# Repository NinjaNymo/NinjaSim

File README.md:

# NinjaSim
A repository for flight simulation stuff, ranging from hardware designs, firmware for said designs, keybind configurations and helpfull scripts.

- `hw/` store KiCad hardware designs and mechanical models.
- `fw/` store firmware for hardware designs.
- `cfg/` store simulator keybinds, HOTAS configurations and OpenTrack profiles. 
- `tools/` store scripts etc.

## Relevant Repostories
- [`NinjaEcadLib`](https://github.com/ninjanymo/ninjaecadlib) - Component library for all hardware designs.
- [`NinjaSim-CDT`](https://github.com/ninjanymo/ninjasim-cdt) - Documentation on how to integrate custom projects into Virpil Control's CDT range of products.

# Overview

## NinjaSim LED Power Board
An adjustable constant current LED driver board desiged for driving three external series IR LEDs for OpenTrack head tracking.

Adjustable current regulation is achieved through an anlog _Voltage-to-Current_ (V-I) regulator. Battery charging is achieved through TI's BQ25185 integrated charger IC where low charging currents are set for safe operation.

Both versions are 2-layered designs with conservative constraints and make extensive use of JLCPCB _Basic Parts_ for cost effective manufacturing.

The two versions differ only in form factor and connector choices.

### `hw/nsim-lpb-v1`

### `hw/nsim-lpb-v2`

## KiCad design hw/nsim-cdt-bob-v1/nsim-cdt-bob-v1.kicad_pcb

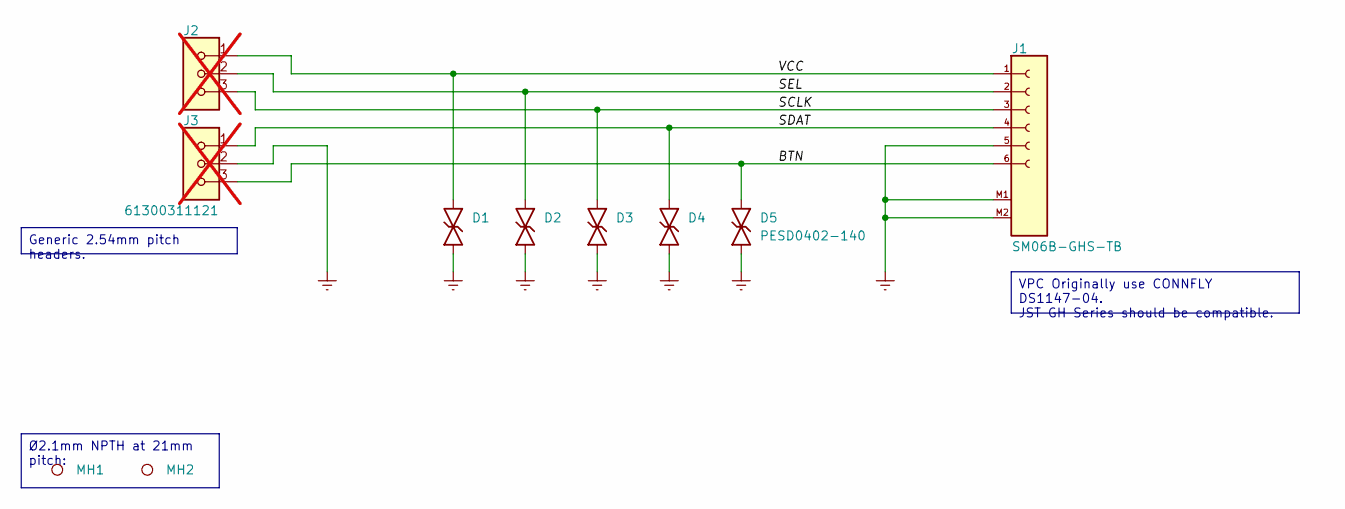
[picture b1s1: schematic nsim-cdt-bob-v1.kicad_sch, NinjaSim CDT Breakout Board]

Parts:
D1, D2, D3, D4, D5: PESD0402-140; RESC1005X45N; Manufacturer_PN PESD0402-140
J1: SM06B-GHS-TB; JST_SM06B-GHS-TB; Manufacturer_PN SM06B-GHS-TB
J2, J3: 61300311121; HDR_254P_03POS_TH_Wurth_WR-PHD; Manufacturer_PN 61300311121; not fitted
MH1, MH2: MH_NPTH_CIR2100

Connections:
/BTN: D5.2 (A), J1.6, J3.3
/SCLK: D3.2 (A), J1.3, J2.3
/SDAT: D4.2 (A), J1.4, J3.1
/SEL: D2.2 (A), J1.2, J2.2
/VCC: D1.2 (A), J1.1, J2.1
GND: D1.1 (K), D2.1 (K), D3.1 (K), D4.1 (K), D5.1 (K), J1.5, J1.M1, J1.M2, J3.2

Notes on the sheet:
Ø2.1mm NPTH at 21mm pitch:
VPC Originally use CONNFLY DS1147-04. JST GH Series should be compatible.
Generic 2.54mm pitch headers.

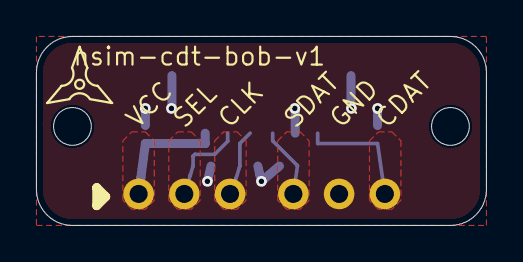
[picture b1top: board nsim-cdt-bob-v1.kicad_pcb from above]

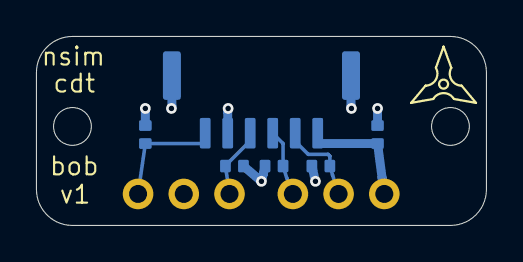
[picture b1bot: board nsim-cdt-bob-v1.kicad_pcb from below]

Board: 2 copper layers, 25.0 x 10.5 mm, 10 parts (6 on the bottom side), 6 nets.

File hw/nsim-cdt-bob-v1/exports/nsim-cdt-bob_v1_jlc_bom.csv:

"Designator","Comment","LCSC Part Number","Package"
"J1","SM06B-GHS-TB","",""
"D5","PESD0402-140","",""
"D4","PESD0402-140","",""
"D3","PESD0402-140","",""
"D2","PESD0402-140","",""
"D1","PESD0402-140","",""
"J3","61300311121","",""
"J2","61300311121","",""

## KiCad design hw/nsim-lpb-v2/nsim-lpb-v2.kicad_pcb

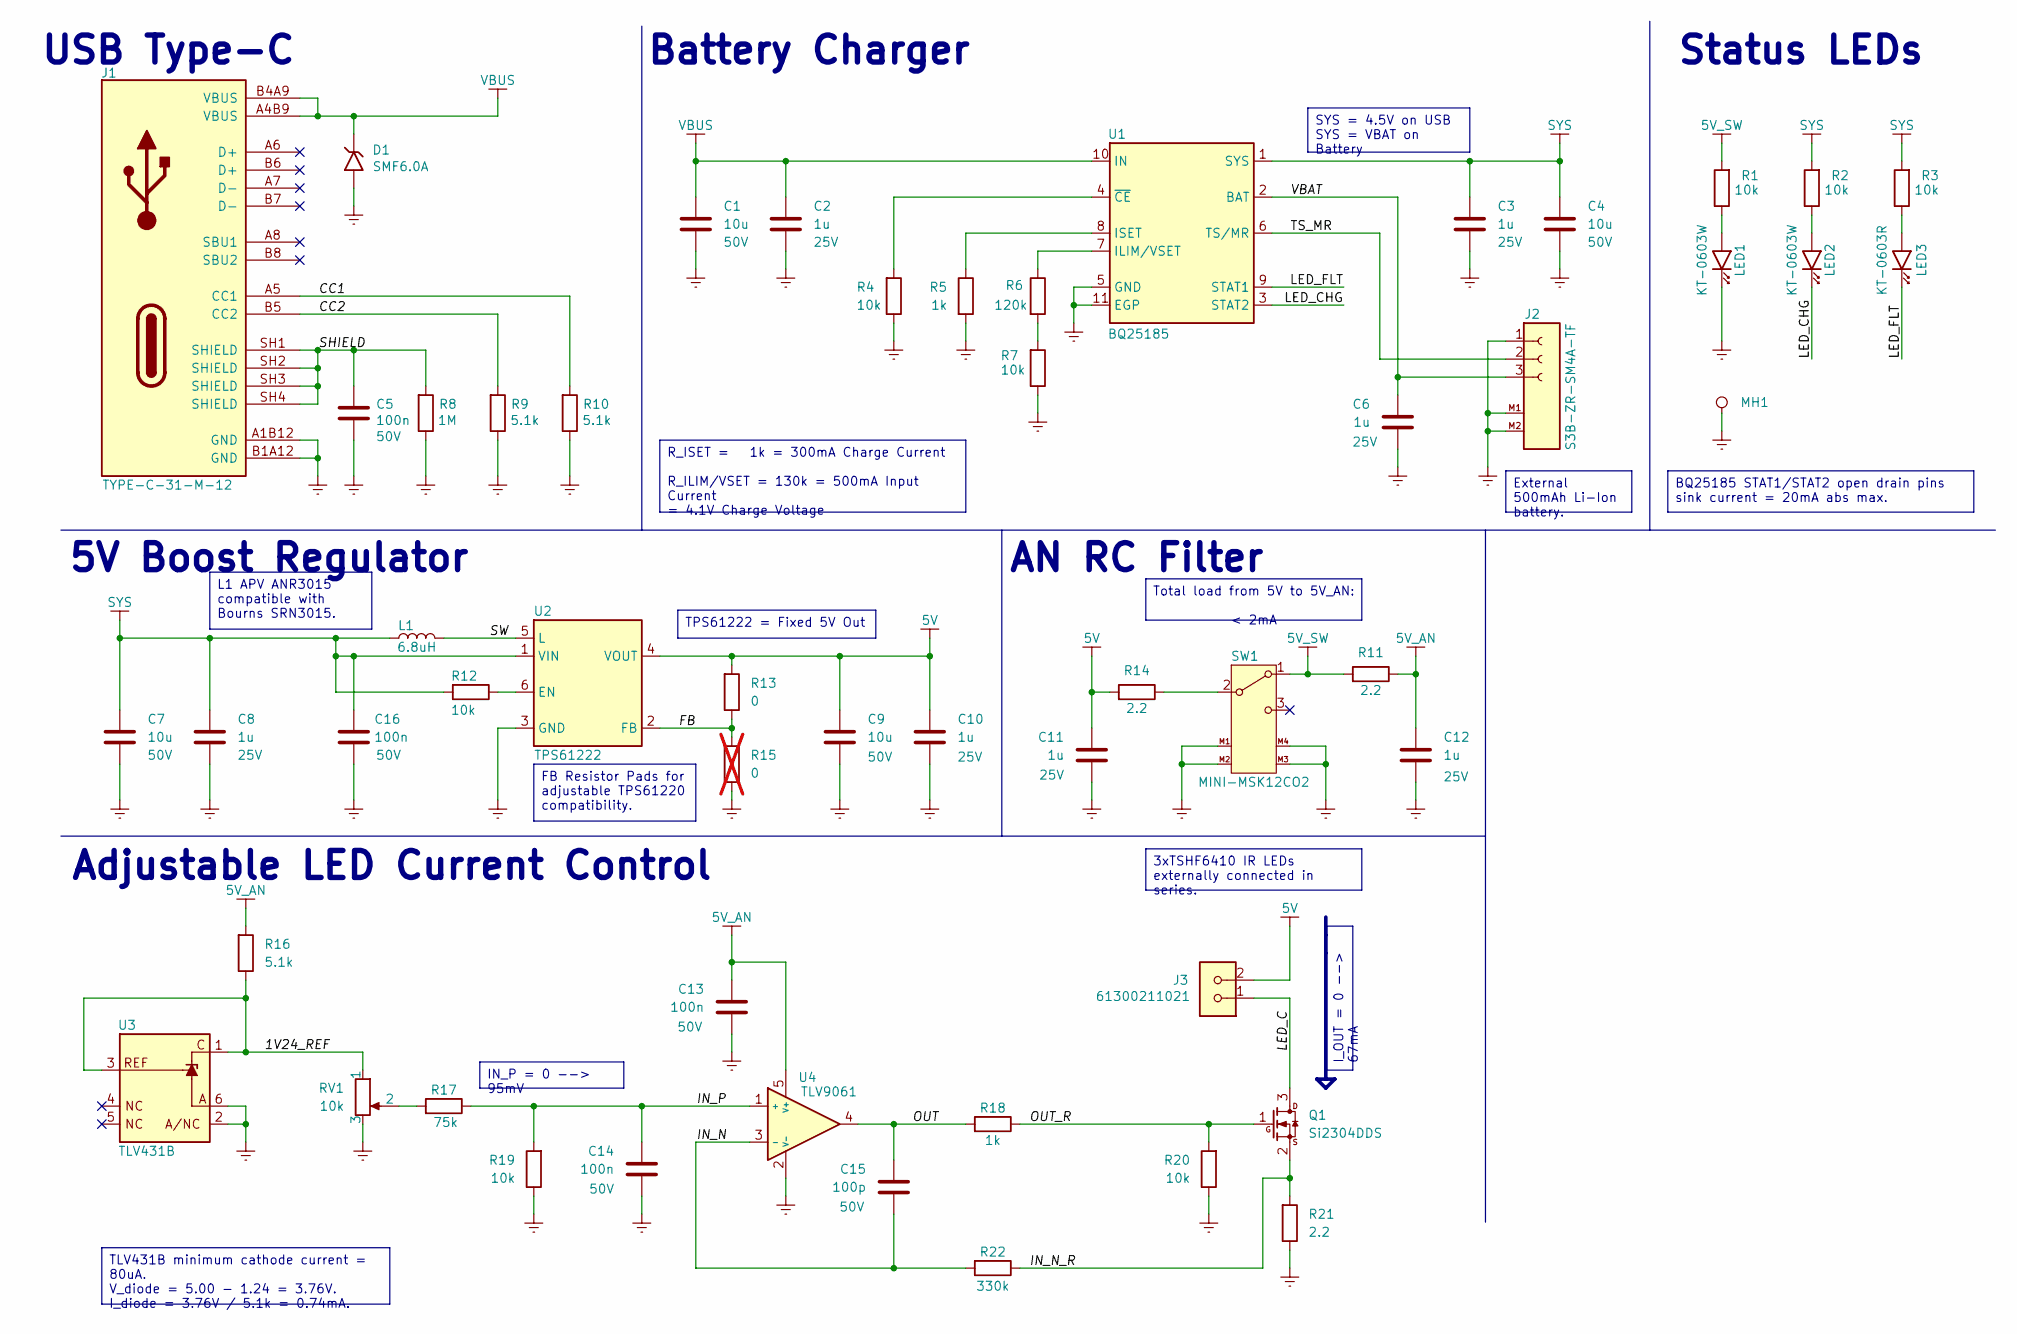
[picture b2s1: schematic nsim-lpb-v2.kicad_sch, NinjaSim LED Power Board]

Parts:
C1, C4, C7, C9: 10u; CAPC3216X180N; Manufacturer_PN CL31A106KBHNNNE; JLC_Package C1206
C2, C3, C6, C8, C10, C11, C12: 1u; CAPC1005X60N; Manufacturer_PN CL05A105KA5NQNC; JLC_Package C0402
C5, C13, C14, C16: 100n; CAPC1005X55N; Manufacturer_PN CL05B104KB54PNC; JLC_Package C0402
C15: 100p; CAPC1005X55N; Manufacturer_PN 0402CG101J500NT; JLC_Package C0402
D1: SMF6.0A; SODFL365X175X110N; Manufacturer_PN SMF6.0A; JLC_Package SOD-123FL
J1: TYPE-C-31-M-12; HRO_TYPE-C-31-M-12; Manufacturer_PN TYPE-C-31-M-12; JLC_Package SMD
J2: S3B-ZR-SM4A-TF; JST_S3B-ZR-SM4A-TF; Manufacturer_PN S3B-ZR-SM4A-TF; JLC_Package SMD,P=1.5mm,Surface Mount，Right Angle
J3: 61300211021; HDR_254P_RA_02POS_TH_Wurth_WR-PHD; Manufacturer_PN 61300211021
L1: 6.8uH; Bourns_SRN3015; Manufacturer_PN ANR3015T6R8M; JLC_Package SMD,3x3mm
LED1, LED2: KT-0603W; LEDC1608X70N_Yellow; Manufacturer_PN KT-0603W; JLC_Package 0603
LED3: KT-0603R; LEDC1608X70N_Red; Manufacturer_PN KT-0603R; JLC_Package 0603
MH1: MH_PTH_CIR7000H3400
Q1: Si2304DDS; SOT95P280X120-3N; Manufacturer_PN Si2304DDS-T1; JLC_Package SOT-23
R1, R2, R3, R4, R7, R12, R19, R20: 10k; RESC1005X40N; Manufacturer_PN 0402WGF1002TCE; JLC_Package R0402
R5, R18: 1k; RESC1005X40N; Manufacturer_PN 0402WGF1001TCE; JLC_Package R0402
R6: 120k; RESC1005X40N; Manufacturer_PN 0402WGF1203TCE; JLC_Package R0402
R8: 1M; RESC1005X40N; Manufacturer_PN 0402WGF1004TCE; JLC_Package R0402
R9, R10, R16: 5.1k; RESC1005X40N; Manufacturer_PN 0402WGF5101TCE; JLC_Package R0402
R11, R14, R21: 2.2; RESC1608X55N; Manufacturer_PN 0603WAF220KT5E; JLC_Package R0603
R13: 0; RESC1005X40N; Manufacturer_PN 0402WGF0000TCE; JLC_Package R0402
R15: 0; RESC1005X40N; Manufacturer_PN 0402WGF0000TCE; JLC_Package R0402; not fitted
R17: 75k; RESC1005X40N; Manufacturer_PN 0402WGF7502TCE; JLC_Package R0402
R22: 330k; RESC1005X40N; Manufacturer_PN 0402WGF3303TCE; JLC_Package R0402
RV1: 10k; Bourns_3314J-1; Manufacturer_PN 3314J-1-103E; JLC_Package SMD,4.5x4.5mm
SW1: MINI-MSK12CO2; ShouHan_MINI-MSK12CO2; Manufacturer_PN MINI MSK12CO2; JLC_Package SMD,5x2.8mm
U1: BQ25185; SON40P220X200X80-11N; Manufacturer_PN BQ25185DLHR; JLC_Package WSON-10-EP(2.2x2)
U2: TPS61222; SOT65P210X110-6N; Manufacturer_PN TPS61222DCKR; JLC_Package SC-70-6(SOT-363)
U3: TLV431B; SOT65P210X110-6N; Manufacturer_PN TLV431BQDCKR; JLC_Package SC-70-6
U4: TLV9061; SOT65P210X110-5N; Manufacturer_PN TLV9061IDCKR; JLC_Package SC-70-5

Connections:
5V: C9.1, C10.1, C11.1, J3.2, R13.1, R14.1, U2.4 (VOUT)
5V_AN: C12.1, C13.1, R11.2, R16.1, U4.5 (V+)
5V_SW: R1.1, R11.1, SW1.1 (A)
/1V24_REF: R16.2, RV1.1, U3.1 (C), U3.3 (REF)
/CC1: J1.A5 (CC1), R10.1
/CC2: J1.B5 (CC2), R9.1
/FB: R13.2, R15.1, U2.2 (FB)
/IN_N: C15.2, R22.1, U4.3 (-)
/IN_N_R: Q1.2 (S), R21.1, R22.2
/IN_P: C14.1, R17.2, R19.1, U4.1 (+)
/LED_C: J3.1, Q1.3 (D)
/LED_CHG: LED2.1 (K), U1.3 (STAT2)
/LED_FLT: LED3.1 (K), U1.9 (STAT1)
/OUT: C15.1, R18.1, U4.4
/OUT_R: Q1.1 (G), R18.2, R20.1
/SHIELD: C5.1, J1.SH1 (SHIELD), J1.SH2 (SHIELD), J1.SH3 (SHIELD), J1.SH4 (SHIELD), R8.1
/SW: L1.2, U2.5 (L)
/TS_MR: J2.2, U1.6 (TS/MR)
/VBAT: C6.1, J2.3, U1.2 (BAT)
GND: C1.2, C2.2, C3.2, C4.2, C5.2, C6.2, C7.2, C8.2, C9.2, C10.2, C11.2, C12.2, C13.2, C14.2, C16.2, D1.2 (A), J1.A1B12 (GND), J1.B1A12 (GND), J2.1, J2.M1 (Pin_3), J2.M2 (Pin_3), LED1.1 (K), MH1.1 (1_1), R4.2, R5.1, R7.2, R8.2, R9.2, R10.2, R15.2, R19.2, R20.2, R21.2, RV1.3, SW1.M1 (A), SW1.M2 (A), SW1.M3 (A), SW1.M4 (A), U1.5 (GND), U1.11 (EGP), U2.3 (GND), U3.2 (A/DNU), U3.6 (A), U4.2 (V-)
unnamed: LED1.2 (A), R1.2
unnamed: LED2.2 (A), R2.2
unnamed: LED3.2 (A), R3.2
unnamed: R6.1, R7.1
unnamed: R17.1, RV1.2
unnamed: R14.2, SW1.2 (B)
unnamed: R6.2, U1.7 (ILIM/VSET)
unnamed: R5.2, U1.8 (ISET)
unnamed: R4.1, U1.4 (~CE)
unnamed: R12.2, U2.6 (EN)
SYS: C3.1, C4.1, C7.1, C8.1, C16.1, L1.1, R2.1, R3.1, R12.1, U1.1 (SYS), U2.1 (VIN)
VBUS: C1.1, C2.1, D1.1 (K), J1.A4B9 (VBUS), J1.B4A9 (VBUS), U1.10 (IN)

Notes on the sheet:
Battery Charger
Adjustable LED Current Control
USB Type-C
AN RC Filter
5V Boost Regulator
Status LEDs
External 500mAh Li-Ion battery.
L1 APV ANR3015 compatible with Bourns SRN3015.
IN_P = 0 --> 95mV
TPS61222 = Fixed 5V Out
SYS = 4.5V on USB SYS = VBAT on Battery
TLV431B minimum cathode current = 80uA. V_diode = 5.00 - 1.24 = 3.76V. I_diode = 3.76V / 5.1k = 0.74mA.
I_OUT = 0 --> 67mA
FB Resistor Pads for adjustable TPS61220 compatibility.
3xTSHF6410 IR LEDs externally connected in series.
Total load from 5V to 5V_AN: < 2mA
R_ISET = 1k = 300mA Charge Current R_ILIM/VSET = 130k = 500mA Input Current = 4.1V Charge Voltage
BQ25185 STAT1/STAT2 open drain pins sink current = 20mA abs max.

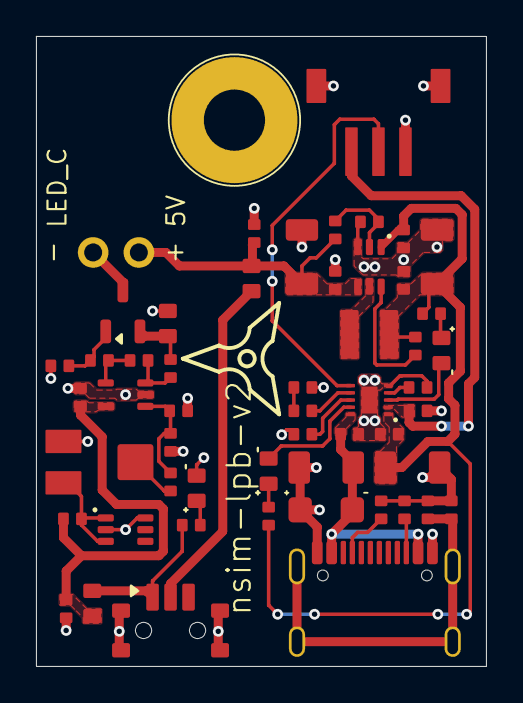
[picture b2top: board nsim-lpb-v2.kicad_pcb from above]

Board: 2 copper layers, 25.0 x 35.0 mm, 54 parts (0 on the bottom side), 32 nets.

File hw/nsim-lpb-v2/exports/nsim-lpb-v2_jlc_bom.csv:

"Designator","Comment","LCSC Part Number","Package"
"J1","TYPE-C-31-M-12","C165948","SMD"
"U2","TPS61222","C116461","SC-70-6(SOT-363)"
"U4","TLV9061","C398357","SC-70-5"
"U3","TLV431B","C2157543","SC-70-6"
"D1","SMF6.0A","C207260","SOD-123FL"
"Q1","Si2304DDS","C56372","SOT-23"
"J2","S3B-ZR-SM4A-TF","C72591","SMD,P=1.5mm,Surface Mount，Right Angle"
"SW1","MINI-MSK12CO2","C2681570","SMD,5x2.8mm"
"LED1","KT-0603W","C2290","0603"
"LED3","KT-0603R","C2286","0603"
"LED2","KT-0603W","C2290","0603"
"U1","BQ25185","C19725033","WSON-10-EP(2.2x2)"
"J3","61300211021","",""
"R8","1M","C26083","R0402"
"R22","330k","C25778","R0402"
"R6","120k","C25750","R0402"
"R17","75k","C25798","R0402"
"RV1","10k","C36376","SMD,4.5x4.5mm"
"R20","10k","C25744","R0402"
"R19","10k","C25744","R0402"
"R12","10k","C25744","R0402"
"R7","10k","C25744","R0402"
"R4","10k","C25744","R0402"
"R3","10k","C25744","R0402"
"R2","10k","C25744","R0402"
"R1","10k","C25744","R0402"
"R16","5.1k","C25905","R0402"
"R10","5.1k","C25905","R0402"
"R9","5.1k","C25905","R0402"
"R18","1k","C11702","R0402"
"R5","1k","C11702","R0402"
"R21","2.2","C22939","R0603"
"R14","2.2","C22939","R0603"
"R11","2.2","C22939","R0603"
"C9","10u","C13585","C1206"
"C7","10u","C13585","C1206"
"C4","10u","C13585","C1206"
"C1","10u","C13585","C1206"
"L1","6.8uH","C7497058","SMD,3x3mm"
"C12","1u","C52923","C0402"
"C11","1u","C52923","C0402"
"C10","1u","C52923","C0402"
"C8","1u","C52923","C0402"
"C6","1u","C52923","C0402"
"C3","1u","C52923","C0402"
"C2","1u","C52923","C0402"
"C16","100n","C307331","C0402"
"C14","100n","C307331","C0402"
"C13","100n","C307331","C0402"
"C5","100n","C307331","C0402"
"C15","100p","C1546","C0402"
"R15","0","C17168","R0402"
"R13","0","C17168","R0402"
